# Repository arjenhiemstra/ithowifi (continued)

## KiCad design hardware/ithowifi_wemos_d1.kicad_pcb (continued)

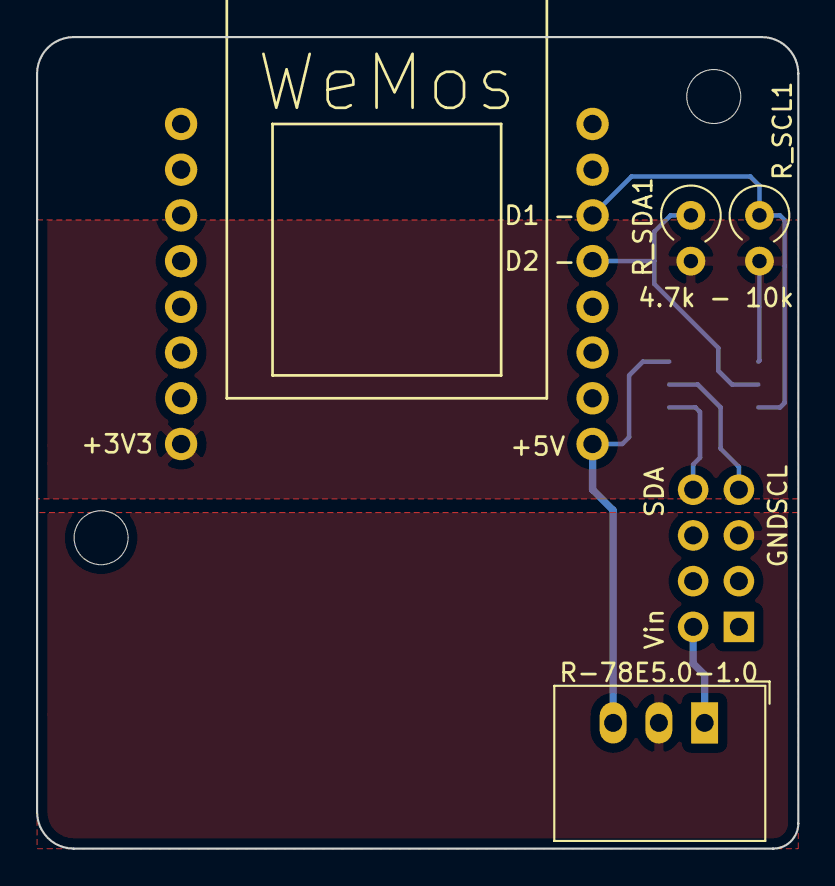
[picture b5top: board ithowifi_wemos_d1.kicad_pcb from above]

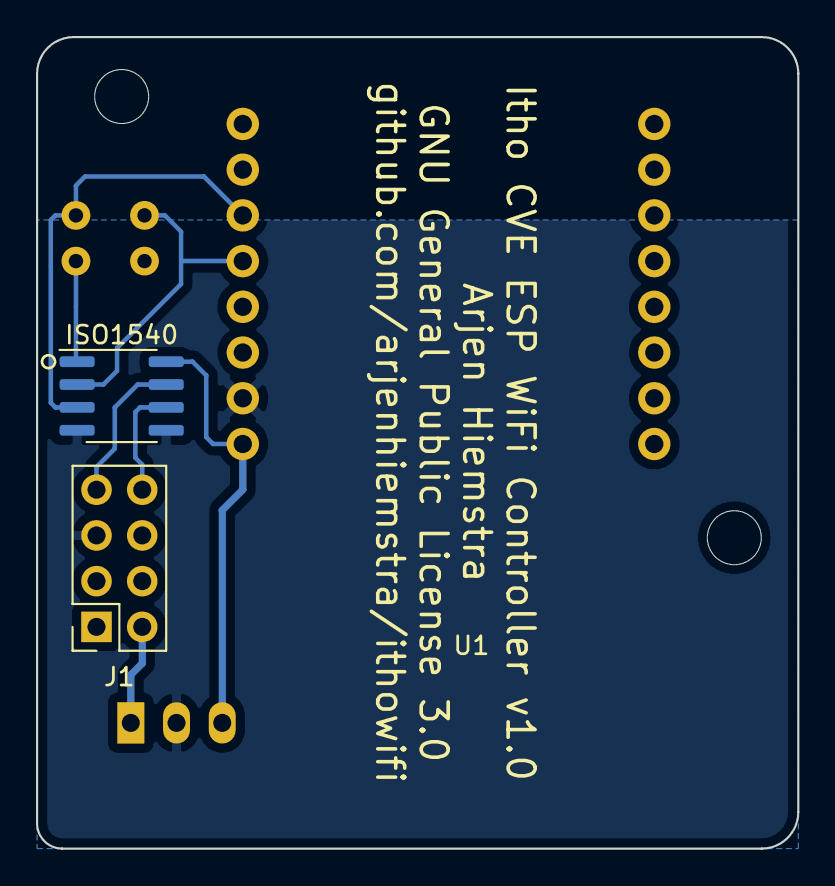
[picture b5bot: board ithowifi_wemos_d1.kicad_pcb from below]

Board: 2 copper layers, 42.3 x 45.1 mm, 8 parts (3 on the bottom side), 8 nets.

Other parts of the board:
 : 3mm; MountingHole_3mm
 #2: 3mm; MountingHole_3mm

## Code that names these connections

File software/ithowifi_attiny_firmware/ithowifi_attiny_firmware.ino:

#define SDAPIN      6 // (PB1)
#define SCLPIN      7 // (PB0)
#define STATUSLED   8 // (PA1)
#define STATUSPIN   2 // (PA6)

#include <Wire.h>

// Global variables
bool mainboardQueryReceived = false;
bool mainboardResponseReceived = false;
bool responseSent = false;

// Static function definitions
void receiveEvent(int howMany);


void receiveEvent(int howMany) {

  (void) howMany;
  while (3 < Wire.available()) { // loop through all but the last 3
    byte c = Wire.read();
  }
  byte received[3];
  received[0] = Wire.read();
  received[1] = Wire.read();
  received[2] = Wire.read();

  if (received[0] == 0x00 && received[1] == 0x00 && received[2] == 0xBE) {
    mainboardQueryReceived = true;
  }
  else if ((received[0] == 0x60 && received[1] == 0x00 && received[2] == 0x4E) ||
           (received[0] == 0x62 && received[1] == 0x00 && received[2] == 0x4C)) {
    mainboardResponseReceived = true;
  }
  else {
    //unknown message
  }

}


void setup() {

  pinMode(STATUSLED, OUTPUT);
  digitalWrite(STATUSLED, LOW);
  pinMode(STATUSPIN, OUTPUT);
  digitalWrite(STATUSPIN, HIGH);

  Wire.begin(77, true);
  Wire.onReceive(receiveEvent);
}

// Main()
void loop() {
  if (!responseSent && (mainboardQueryReceived || millis() > 250)) {
    mainboardQueryReceived = false;

    while (digitalRead(SCLPIN) == LOW) {
    }

    Wire.end();

    delay(10);

    //Write response as to itho fan i2c master
    Wire.begin();

    Wire.beginTransmission(byte(0x41));
    Wire.write(byte(0xEF));
    Wire.write(byte(0xC0));
    Wire.write(byte(0x00));
    Wire.write(byte(0x01));
    Wire.write(byte(0x06));
    Wire.write(byte(0x00));
    Wire.write(byte(0x00));
    Wire.write(byte(0x09));
    Wire.write(byte(0x00));
    Wire.write(byte(0x09));
    Wire.write(byte(0x00));
    Wire.write(byte(0xB6));
    Wire.endTransmission(true);

    Wire.end();
    responseSent = true;

    //Switch to i2c slave again and wait for the reply
    Wire.begin(77, 1);
    Wire.onReceive(receiveEvent);

  }
  if (mainboardResponseReceived) {
    mainboardResponseReceived = false;

    //disable i2c
    Wire.end();

    //put i2c pins in high-impedance state
    pinMode(SDAPIN, INPUT);
    pinMode(SCLPIN, INPUT);

    //set status
    digitalWrite(STATUSLED, HIGH);//switch status led off
    digitalWrite(STATUSPIN, LOW); //signal Wemos that init has finished successful

  }

}

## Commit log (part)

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2026-03-18 build: update ArduinoStreamUtils to v1.9.2 and ArduinoJson to v7.4.3
2026-03-21 feat: add RF binding initiator support
    Enable the firmware to initiate RF binding as an RFT Auto-N remote.
    The binding flow:
    1. Send Binding Offer (1FC9 I, self-addressed)
    2. Receive Binding Accept (1FC9 W from target)
    3. Send Binding Confirm (1FC9 I, payload 00, to target)
    4. Send Battery Status (1060 x3)
2026-03-21 feat: add rfco2 and rfdemand API support for CO2 remote emulation
    Expose CO2 value (1298) and ventilation demand (31E0) sending through
    all interfaces:
    - WebAPIv2: rfco2, rfdemand, rfzone parameters
    - MQTT API: rfco2, rfdemand, rfzone JSON keys
    - Websocket: rfco2, rfdemand handlers for web UI
    - Web UI: CO2 input + Send CO2 button, Demand input + Send Demand
2026-03-22 feat: add OpenAPI spec endpoint and Swagger UI page
    Add /api/openapi.json endpoint that dynamically generates an OpenAPI
    3.0.3 specification with all API parameters, response schemas, and
    MQTT command documentation. Includes CORS header for external tools.
    Add Swagger UI as an SPA page (html_swagger.html) that loads the
    interactive API explorer from jsDelivr CDN. Accessible via the
    "Interactive API Explorer" link on the API page. Falls back to
2026-03-22 test: add websocket, response format, and config endpoint tests
    Stage 1 expansion of test coverage:
    - test_websocket.py: 25 tests for websocket data queries, commands,
    and edge cases (empty/invalid JSON, rapid messages, large payloads)
    - test_response_format.py: 24 tests for JSend format validation,
    config file endpoints (config.json, remotes.json, wifi.json),
    password masking, destid/bidirectional fields, virtual remote commands
2026-03-22 test: add persistence, spec completeness, security, and MQTT state tests
    Category 4 - Config persistence (7 tests):
    Reboot device, verify remotes/destID/bidirectional/RF module ID survive
    Category 5 - OpenAPI spec completeness (17 tests):
    Every WebAPI processor has matching spec params, all enum values
    documented, MQTT schema covers all JSON keys
    Category 6 - Security (18 tests):
2026-03-23 feat: migrate all users to WebAPI v2 on upgrade to 3.0.0
    Change api_version semantics: 0=v1 (legacy), anything else=v2+.
    Old configs with api_version=1 (from v2.8.x) are now treated as v2
    since 1 is not 0. Users can still explicitly select "1 (legacy)"
    which stores 0. No migration code or NVS flags needed.
2026-03-26 feat: add all GET endpoints for RESTful API v2
    GET /api/v2/speed - current fan speed
    GET /api/v2/status - Itho device status
    GET /api/v2/device - device info (type, firmware, hardware)
    GET /api/v2/queue - command queue with speed info
    GET /api/v2/lastcmd - last executed command
    GET /api/v2/remotes - RF remotes configuration
2026-03-26 feat: add CORS headers to all API endpoints
    Add Access-Control-Allow-Origin: * to all API responses:
    - REST /api/v2/* endpoints via response helpers
    - Legacy /api.html via AsyncWebServerAdapter
    - OPTIONS preflight handlers for all /api/v2/ endpoints
    This enables cross-origin access from Home Assistant dashboards,
    Node-RED, Swagger UI on different hosts, and other web tools.
2026-03-26 docs: correct API table v1 availability markers
    Fix WebAPI v1 column markers in the API documentation table to
    accurately reflect which commands are available on the legacy
    /api.html endpoint:
    Changed to ◌ (not available on v1):
    - get=deviceinfo, get=rfstatus, get=vremotesinfo
    - rfco2, rfdemand, rfzone
2026-03-26 refactor: rename REST API v2 endpoints for clarity
    Group RF endpoints under /api/v2/rfremote/:
    /api/v2/rfremote/command (was /rfremote)
    /api/v2/rfremote/co2 (was /rfco2)
    /api/v2/rfremote/demand (was /rfdemand)
    /api/v2/rfremote/config (was /rf/config)
    Rename for consistency with existing naming:
2026-03-26 fix: auto-save remote config before entering learn/leave mode
    When the user clicks Learn/Leave, auto-save the currently selected
    remote's config (function, type, name, ID) before sending the
    learn/leave command. This ensures that if the user changed the
    remote to Monitor mode but forgot to click Update, the device
    has the correct function and won't send a join reply.
    200ms delay between save and learn/leave to ensure the config
2026-03-27 fix: remove build warnings and deprecated API calls
    Remove unused delegateToProcessor function (-Wunused-function).
    Replace all deprecated containsKey() with isNull() checks per
    ArduinoJson v7 migration guide (-Wdeprecated-declarations).
    Rename test function to match.
    Zero warnings from project code.
2026-03-27 feat: add itho_rf_co2_join and itho_control_interface settings
    New system config fields for RF CO2 control mode:
    - itho_rf_co2_join (default 0): 0=off, 1=send RF CO2 join on next
    boot. Auto-resets to 0 after join is sent.
    - itho_control_interface (default 0): 0=virtual remote (I2C buttons),
    1=RF CO2 (RF buttons + demand slider). Auto-set to 1 when RF CO2
    join succeeds.
2026-03-27 feat: add RF CO2 control settings to system settings page
    Add to CC1101 section in system settings:
    - Control interface: Virtual remote (I2C) / RF CO2 (demand slider)
    - Send RF CO2 join: next power on / off
    Both settings included in the system settings save message.
2026-03-27 fix: set sourceID for Send remotes at boot and on config update
    For remotes with function=Send, the configured ID is the sourceID
    (what the add-on transmits as). This was not being set in the
    runtime ithoRF device array, causing sendRFCommand to fall back
    to the module's defaultID instead of the configured remote ID.
    Now calls updateSourceID:
    - At boot when loading remotes from flash
2026-03-27 fix: restore sourceID for Send remotes (needed for correct TX identity)
    The previous revert was wrong — the sourceID fix IS needed. Without
    it, sendRFCommand falls back to defaultID (module RF ID) which can
    be a different device type than what the Itho was joined with.
    Example: remote joined as 56:022609 but commands sent as 48:081847
    because defaultID is in type-48 range. The Itho ignores commands
    from an unknown source.
2026-03-27 feat: disable TX power dropdown until remote is selected
    TX power dropdown starts disabled. Enabled when the remote's
    radio button is selected, disabled for all others.
2026-03-28 feat: add percentage and fandemand to POST /api/v2/command
    New keys for unified fan control:
    - percentage (0-100): maps to device-appropriate command
    - fandemand (0-200): direct demand value
    Behavior based on device capability:
    - RF CO2 (itho_control_interface=1): sends auto + rfdemand via
    first Send+RFTCO2 remote
2026-03-28 feat: show actual fan demand on index page slider
    Store the last demand value sent via ithoSendRFDemand in global
    ithoFanDemand. Include as fan_demand in systemstat websocket
    message. Index page slider updates to reflect the demand.
    Previous approach (parsing 31DA response) was wrong — byte 1 of
    31DA is AirQuality not demand, and 0xEF means unavailable. Now
    tracks what we actually sent instead.
2026-03-29 fix: coredump download crash due to use-after-free
    The handleCoredumpDownload handler had multiple bugs:
    - Lambda captured local stack buffer by reference (use-after-free)
    - Read data into wrong buffer (local vs callback parameter)
    - No null check on partition iterator
    - Iterator never released
    Rewrote to read directly into the callback buffer, check for
2026-03-30 feat: OTA firmware update from GitHub releases
    Add online firmware update functionality with version selection dropdown
    populated from firmware.json. Users can install any available stable or
    beta version directly from the web UI, MQTT, REST API, or Home Assistant.
    Changes:
    - HTTPUpdate-based OTA download with progress tracking
    - Version dropdown with firmware.json support for older releases
2026-04-01 feat: RF standalone mode for devices without I2C
    Adds support for controlling Itho devices that have no I2C connector
    (e.g. HRU 400) via RF only using a CC1101 module as an RFT CO2 remote.
    Firmware changes:
    - SystemConfig: itho_rf_standalone field
    - task_syscontrol: skip all I2C init/queries in standalone mode
    - task_cc1101: auto-track Itho device as RF status source on bind accept
2026-04-04 build: version 3.0.0
2026-04-06 build: version 3.1.0-beta1
2026-04-06 ci: remove old main.yml workflow from master
2026-04-10 release: point firmware.json at 3.1.0-beta2
2026-04-11 release: point firmware.json at 3.1.0-beta4
2026-04-12 fix: add 3.0.0 to firmware dropdown, remove stale IthoSystem files
    - Add 3.0.0 to the versions array in firmware.json so users can
    downgrade from 3.1.0 via the Update page dropdown.
    - Remove IthoSystem.cpp/.h from master — these were deleted during
    the 3.0.0 code restructuring but survived on master, causing CI
    build failures (references to renamed symbols rf, add2queue).
2026-04-12 docs: consolidate 3.1.x release notes, mark 3.1.0/3.1.1 as superseded
2026-04-13 fix: remove 2.8.0 from versions list (key collision with old update page)
2026-05-29 feat: FanInfo-aware RF demand dispatch + diagnostics for #365
    RFT CO2 demand dispatch (websocket index slider, REST /api/v2/command,
    MQTT cmd) now reads the unit's FanInfo (from ithoMeasurements 31DA
    when itho_31da=1, else from sniffed rfStatusSources[*].measurements31DA)
    and only precedes the 31E0 demand with an 'auto' RF command when
    FanInfo is not 'auto'. Avoids the boost-mode side-effect that dropped
    subsequent lower demand values when the unit was already in auto.
2026-05-29 release: firmware.json beta -> 3.1.4-beta4
2026-06-05 fix: remove 2.8.0 from versions list (2.8.x update-page collision)
    The 2.8.x web UI's traverse() function matches the version string
    "2.8.0" against the hw_rev key "2" and resolves the wrong link,
    so a user on 2.8.0 sees the latest as 3.1.3 but clicking download
    fetches 2.8.0 again. Removing the 2.8.0 entry is the same fix we
    applied previously (reverted at some point).
    2.8.1 stays as the available downgrade target on the dropdown.
2026-06-08 Revert "fix: periodic PWM2I2C init re-send for CVE ECO 2 SP (#365)"
    This reverts commit 7643d779dde3521b7b71098153659d0116a4a301.
2026-06-08 release: version 3.1.4-beta7
2026-06-09 release: sync firmware.json for 3.1.4
2026-06-10 feat: accept multi-zone 31DA / 31D9 frames (#366)
    parseRF31DA and parseRF31D9 dropped every frame whose first payload
    byte wasn't 0, treating it as an "unexpected domain byte". On Itho
    DuoZone HRUs (e.g. HRU ECO 300 R 03-00630 in #366) the unit
    broadcasts the same opcode once per zone with the zone ID in that
    byte (0x15 / 0x16 / 0x17), so every frame was dropped and the source
    looked offline on /api/v2/rfstatus.
2026-06-11 fix: RF status request — log at info, dropdown shows slot indices
    Two follow-ups on the new debug-page RF status request flow:
    - sendRFStatusRequest used D_LOG so the "sent RF 31DA+31D9 status
    request via remote idx:N" line was filtered out at the default log
    level, making the debug button look like a no-op. Bumped to I_LOG;
    it's a user-initiated diagnostic action, not chatty enough to crowd
    the log.
2026-06-12 fix: paired RF status request was dropping the second opcode
    The combined 31DA + 31D9 request stuffed both sendRQ frames into one
    disableRF_ISR/enableRF_ISR critical section back-to-back. The CC1101
    was still in an intermediate state from the first TX when the second
    sendRQ tried to run — first opcode went out cleanly, second silently
    didn't. Observable on .246's periodic standalone-mode poll: every
    poll cycle produced a 31DA RQ on the air, no 31D9 at all.
2026-06-13 release: version 3.2.0-beta2
2026-06-13 release: version 3.3.0-beta1
